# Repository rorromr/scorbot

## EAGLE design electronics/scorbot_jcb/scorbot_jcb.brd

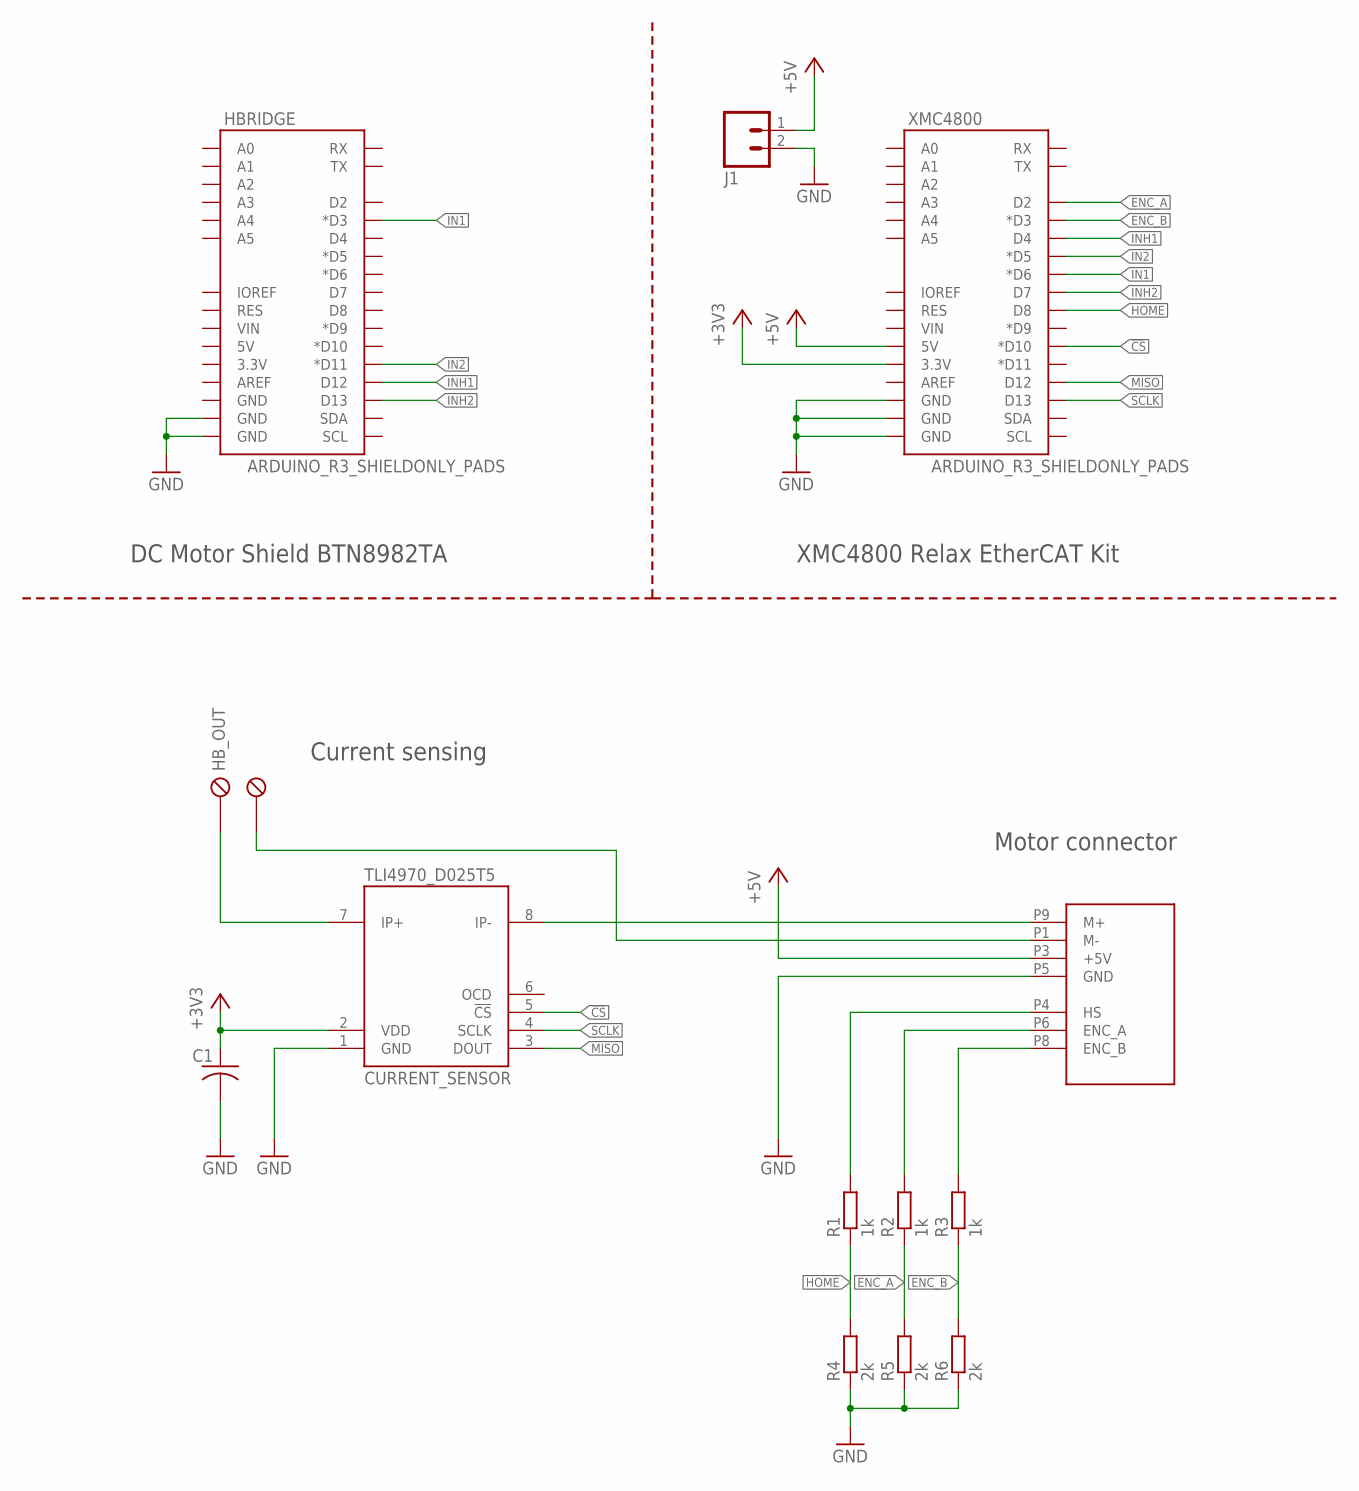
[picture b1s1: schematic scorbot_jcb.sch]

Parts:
C1: C-US025-025X050; C025-025X050
CURRENT_SENSOR: TLI4970_D025T5
DB9: SCORBOT_CONNECTOR; XM3-LS
HBRIDGE: ARDUINO_R3_SHIELDONLY_PADS; UNO_R3_SHIELD_ONLY_PADS
HB_OUT: METALTEX-2SHORT; METALTEX-2S
J1: M02LOCK_LONGPADS; 1X02_LOCK_LONGPADS
R1, R2, R3: 1k; 0309/12
R4, R5, R6: 2k; 0309/12
XMC4800: ARDUINO_R3_SHIELDONLY_PADS; UNO_R3_SHIELD_ONLY_PADS

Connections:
!CS: CURRENT_SENSOR.5 (!CS), XMC4800.D10 (*D10)
+3V3: C1.1, CURRENT_SENSOR.2 (VDD), XMC4800.3.3V
+5V: DB9.P3 (+5V), J1.1, XMC4800.5V
ENC_A: R2.1, R5.2, XMC4800.D2
ENC_B: R3.1, R6.2, XMC4800.D3 (*D3)
GND: C1.2, CURRENT_SENSOR.1 (GND), DB9.P5 (GND), HBRIDGE.GND@0 (GND), HBRIDGE.GND@1 (GND), J1.2, R4.1, R5.1, R6.1, XMC4800.GND@0 (GND), XMC4800.GND@1 (GND), XMC4800.GND@2 (GND)
HOME: R1.1, R4.2, XMC4800.D8
IN1: HBRIDGE.D3 (*D3), XMC4800.D6 (*D6)
IN2: HBRIDGE.D11 (*D11), XMC4800.D5 (*D5)
INH1: HBRIDGE.D12, XMC4800.D4
INH2: HBRIDGE.D13, XMC4800.D7
MISO: CURRENT_SENSOR.3 (DOUT), XMC4800.D12
unnamed: CURRENT_SENSOR.8 (IP-), DB9.P9 (M+)
unnamed: CURRENT_SENSOR.7 (IP+), HB_OUT.P1
unnamed: DB9.P1 (M-), HB_OUT.P2
unnamed: DB9.P4 (HS), R1.2
unnamed: DB9.P6 (ENC_A), R2.2
unnamed: DB9.P8 (ENC_B), R3.2
SCLK: CURRENT_SENSOR.4 (SCLK), XMC4800.D13

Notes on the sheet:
Current sensing
Motor connector
XMC4800 Relax EtherCAT Kit
DC Motor Shield BTN8982TA

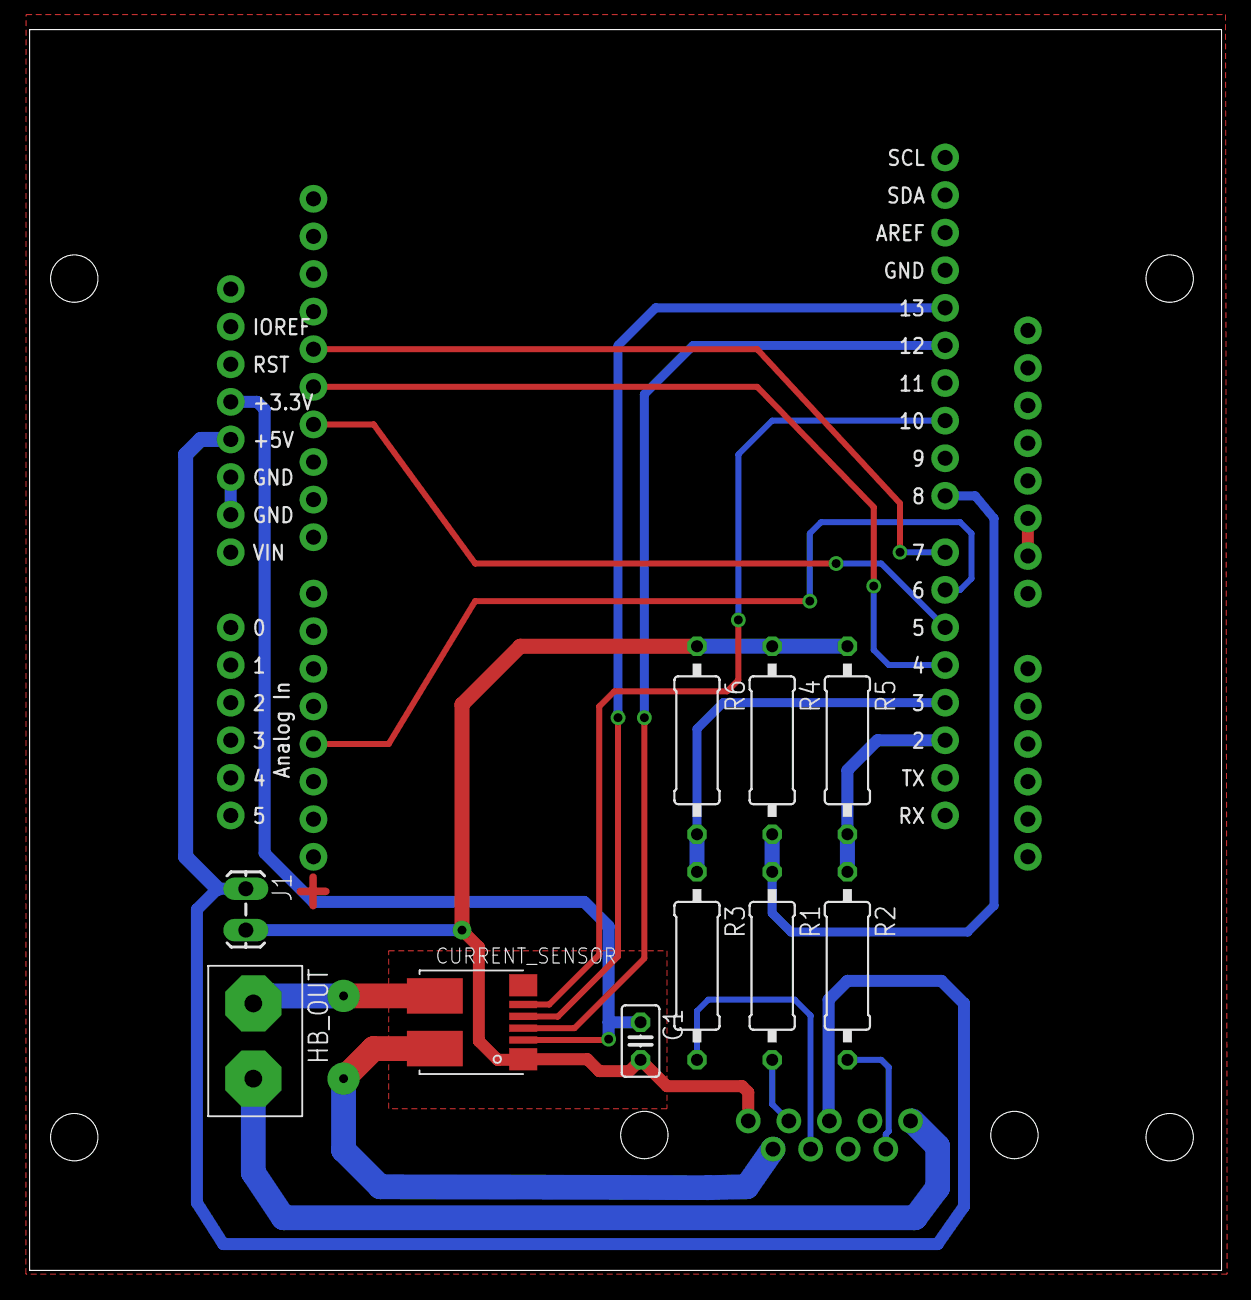
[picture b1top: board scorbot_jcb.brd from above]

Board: 2 copper layers, 80.5 x 83.8 mm, 13 parts (1 on the bottom side), 19 nets.

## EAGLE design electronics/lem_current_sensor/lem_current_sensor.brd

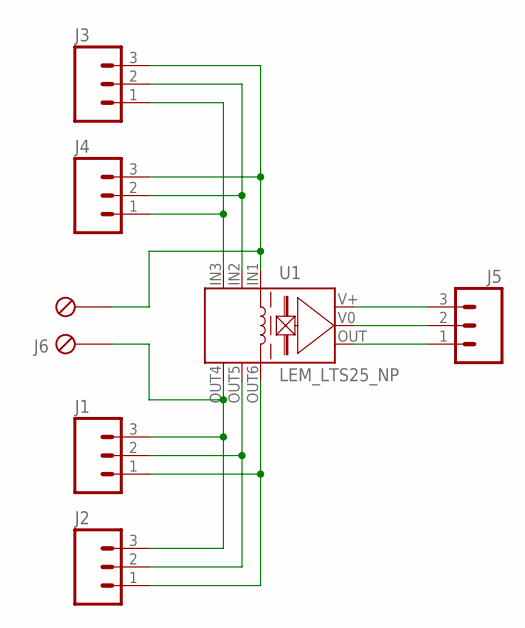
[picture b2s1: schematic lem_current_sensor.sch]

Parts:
J1, J2, J3, J4, J5: M03LONGPADS; 1X03_LONGPADS
J6: METALTEX-2
U1: LEM_LTS25_NP; LTS25_NP

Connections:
GND: J5.2, U1.V0 (0V)
IP+: J3.3, J4.3, J6.P2, U1.IN1
IP-: J1.3, J2.3, J6.P1, U1.OUT4
unnamed: J1.2, J2.2, U1.OUT5
unnamed: J1.1, J2.1, U1.OUT6
unnamed: J3.1, J4.1, U1.IN3
unnamed: J3.2, J4.2, U1.IN2
unnamed: J5.1, U1.OUT (VOUT)
unnamed: J5.3, U1.V+

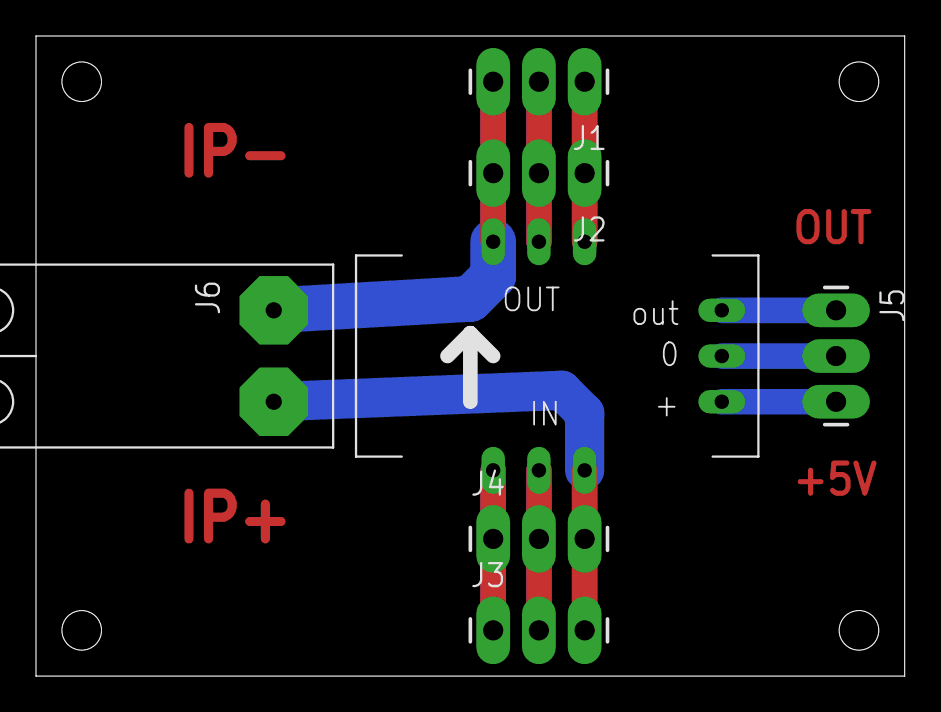
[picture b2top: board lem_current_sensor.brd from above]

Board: 2 copper layers, 48.3 x 35.6 mm, 7 parts (0 on the bottom side), 9 nets.

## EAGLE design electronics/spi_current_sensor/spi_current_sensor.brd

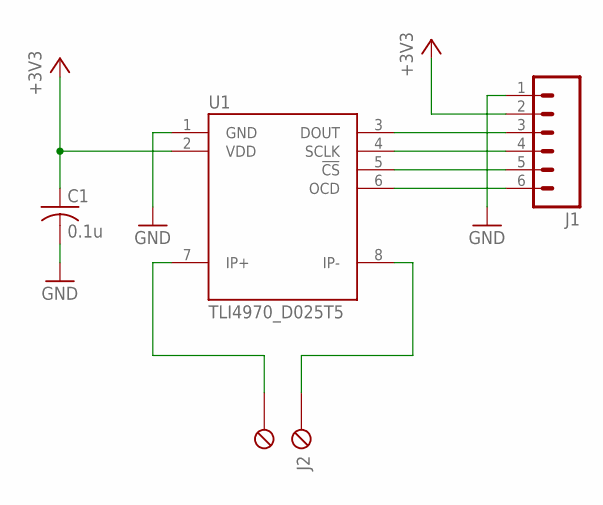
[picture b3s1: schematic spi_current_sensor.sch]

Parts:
C1: 0.1u; C025-025X050
J1: M06LONGPADS; 1X06_LONGPADS
J2: METALTEX-2
U1: TLI4970_D025T5

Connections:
+3V3: C1.1, J1.2, U1.2 (VDD)
GND: C1.2, J1.1, U1.1 (GND)
unnamed: J1.3, U1.3 (DOUT)
unnamed: J1.4, U1.4 (SCLK)
unnamed: J1.5, U1.5 (!CS)
unnamed: J1.6, U1.6 (OCD)
unnamed: J2.P2, U1.7 (IP+)
unnamed: J2.P1, U1.8 (IP-)

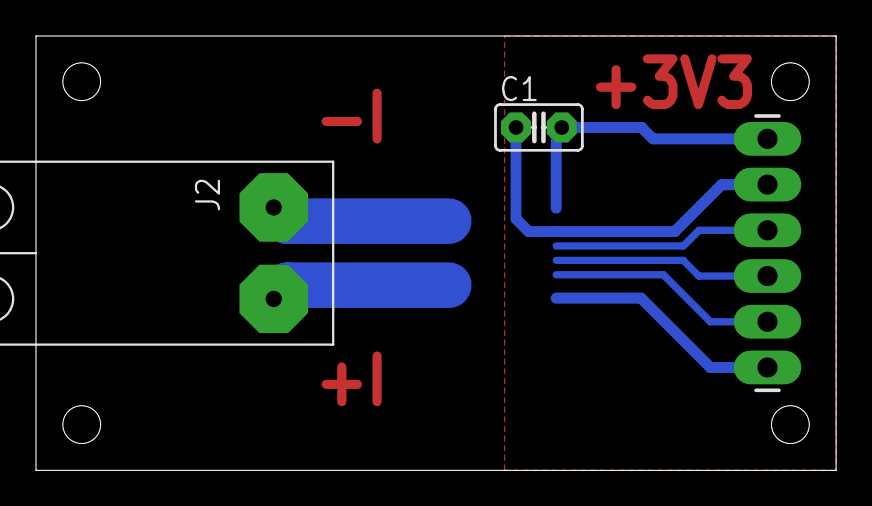
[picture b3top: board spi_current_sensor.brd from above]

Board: 2 copper layers, 44.5 x 24.1 mm, 4 parts (1 on the bottom side), 8 nets.

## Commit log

2016-10-25 SPI current sensor
2016-10-25 Add decoupler capacitor to current sensor
2016-10-25 LEM current sensor
2016-10-28 Fix dimensions and MATLAB script for motor constants
2016-11-17 TLI4970 current sensor
2016-11-21 Current sensor TLI4970 and basic PWM generator
2016-11-23 POSIF1 interface for XMC4800
2016-11-25 Interrupt based quadrature encoder interface
2016-11-28 TLI and interrupt encoder
2016-11-29 HBridge interface
2016-12-01 H bridge test
2016-12-01 Fix merge
2016-12-28 URDF and Gazebo files
2017-01-03 Motor 9413 parameter estimation
2017-01-03 9434 motor parameters
2017-01-04 Symbolic controller design
2017-01-05 DSP format for controller design
2017-01-05 Scorbot EtherCAT driver test
2017-01-11 scorbot control board
2017-01-12 Current sensor
2017-01-12 Schematic for shield
2017-01-12 Board init design
2017-01-16 Ruteo
2017-03-07 Base ethercat
2017-03-09 Basic ecat driver
2017-03-11 ros_control interface
2017-03-14 Fixed Ethercat driver configure
2017-03-15 Joint position
2017-03-17 Add joint limits params
2017-03-20 Phantom install
2017-03-22 Add joint limits
2017-03-22 Fix omni deps
2017-03-22 Init Haptics
2017-03-23 Basic haptic mapping functions
2017-03-23 Encoder mapping and topic remap
2017-03-23 Haptic test
2017-03-28 Fix board orientation
2017-04-26 Add runtime instructions
2017-05-11 Holes and via correction
2017-05-12 Digital PID test
2017-06-15 Add integral and euler
2017-06-21 Add shoulder controller
2017-06-22 Test with haptic force and shoulder
2017-07-03 Tracking result
2017-07-03 Add force data
2017-08-17 Better visualization and elbow mapping
2017-12-29 Add cad files
2018-01-09 Fix install path
2018-01-20 Add scorbot shadow
2018-03-15 Add EtherCAT code
2018-04-03 Matlab plots for results
2018-04-10 Add float parameter
2018-04-14 Current mode
2018-04-17 Current data
2018-04-18 Add plots
2018-04-21 Add 4 joints
2018-05-01 Add all joints with new panel
2018-05-05 Effort controller for gripper
2018-05-08 Add timeout parameters
2018-05-13 Add current data
2018-05-14 Add gripper limitation
2018-05-27 Add speed test
2018-05-31 Add current limitation sung dynamic reconfigure
2018-05-31 Add current factor and default value
2018-06-18 speed observer results
2018-06-19 Add speed controller discretization
2018-07-19 Add basic motor model
2018-07-19 Add sym code
2018-08-05 Motor model
2018-08-13 Add motor z test
2018-08-20 speed controller from estimator
2018-08-20 Add B in motors
2018-08-25 Add open loop
2018-09-23 Add gripper CAD
2018-09-23 Change in open loop test
2018-09-24 fix gripper distances
2018-09-24 Add gripper frames
2018-09-26 Add texture, fix gripper center
2018-10-22 Add speed controller
2018-10-23 Positio controller
2018-10-26 Position controller feedback
2018-10-29 Add position controller and speed plant integrator
2018-10-29 Add folders and sort files
2018-10-29 Add basic params
2018-11-01 initial commit: ros-melodic rviz/gazebo scorbot model port. Added position/effort/trajectory controllers fro gazebo model. Added gripper.
2018-12-17 Add ramp generator
2019-02-24 Add dae for body and base
2019-02-24 Add dae frames
2019-03-04 Add dae meshes for gripper model
2019-03-04 Add DAE generation steps
2019-03-04 Add vm snapshot
2019-03-09 Fix gripper TF
2019-03-09 Add Gripper urdf based on dae files
2019-03-10 Add collition model based in basic shapes
2019-03-11 Add fix for melodic
2019-03-23 Disable gripper
2019-03-28 Add gripper links
2019-03-28 Add joint name print
2019-04-01 Add control_toolbox dep
2019-04-01 Fix description, remove old gripper
2019-04-01 Add launch for robot description
2019-04-03 Fix Scorbot gazebo ros_control for Indigo
2019-04-04 Fix gazebo sim deps, fix textures, add world to base fixed joint
2019-04-05 Add moveit config
2019-04-06 Add default current and ecat parameter
2019-04-06 Fix dynamic reconfigure
2019-04-06 Add calibration offset
2019-04-06 Joint trajectory controller
2019-04-08 Fix namespace for description and moveit
2019-04-10 Test controller on scorbot
2019-04-12 Add limits and parameters in driver
2019-04-13 Fix encoder mapping
2019-04-13 Add gripper driver
2019-05-11 Add tf prefix scorbot
2019-05-12 Add tf prefix in moveit
2019-05-12 Add controller timeout
2019-06-15 Add proxy algorithm
2019-06-17 Add sampling and proxy algorithm
2019-06-22 Add marker
2019-06-23 Add tf marker, fix marker size
2019-06-28 Add contact movement
2019-07-01 Fix arrows
2019-07-05 Add dynamic reconfigure and library
2019-08-10 Change marker folder
2019-08-10 Add launch file, fix markers args
2019-08-11 Add phantom mapping
2019-08-17 Fix force trigger, set logger to debug, add rqt
2019-08-24 Fix perspective, add enable gripper
2019-08-24 Fix shadow launch
2019-08-25 Add proxy to shadow robot
2020-02-13 add current controller
